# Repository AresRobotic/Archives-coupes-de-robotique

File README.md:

Archives-coupes-de-robotique
============================

Ce dépot contient l'ensemble des documents techniques, codes, cartes et autres des robots des années précédentes.

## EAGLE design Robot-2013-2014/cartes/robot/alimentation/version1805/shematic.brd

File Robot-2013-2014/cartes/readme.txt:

cartes à jour et transmises en fab à Dipole

il faut regenerer toutes les images et tableaux wiki de chaque cartes.

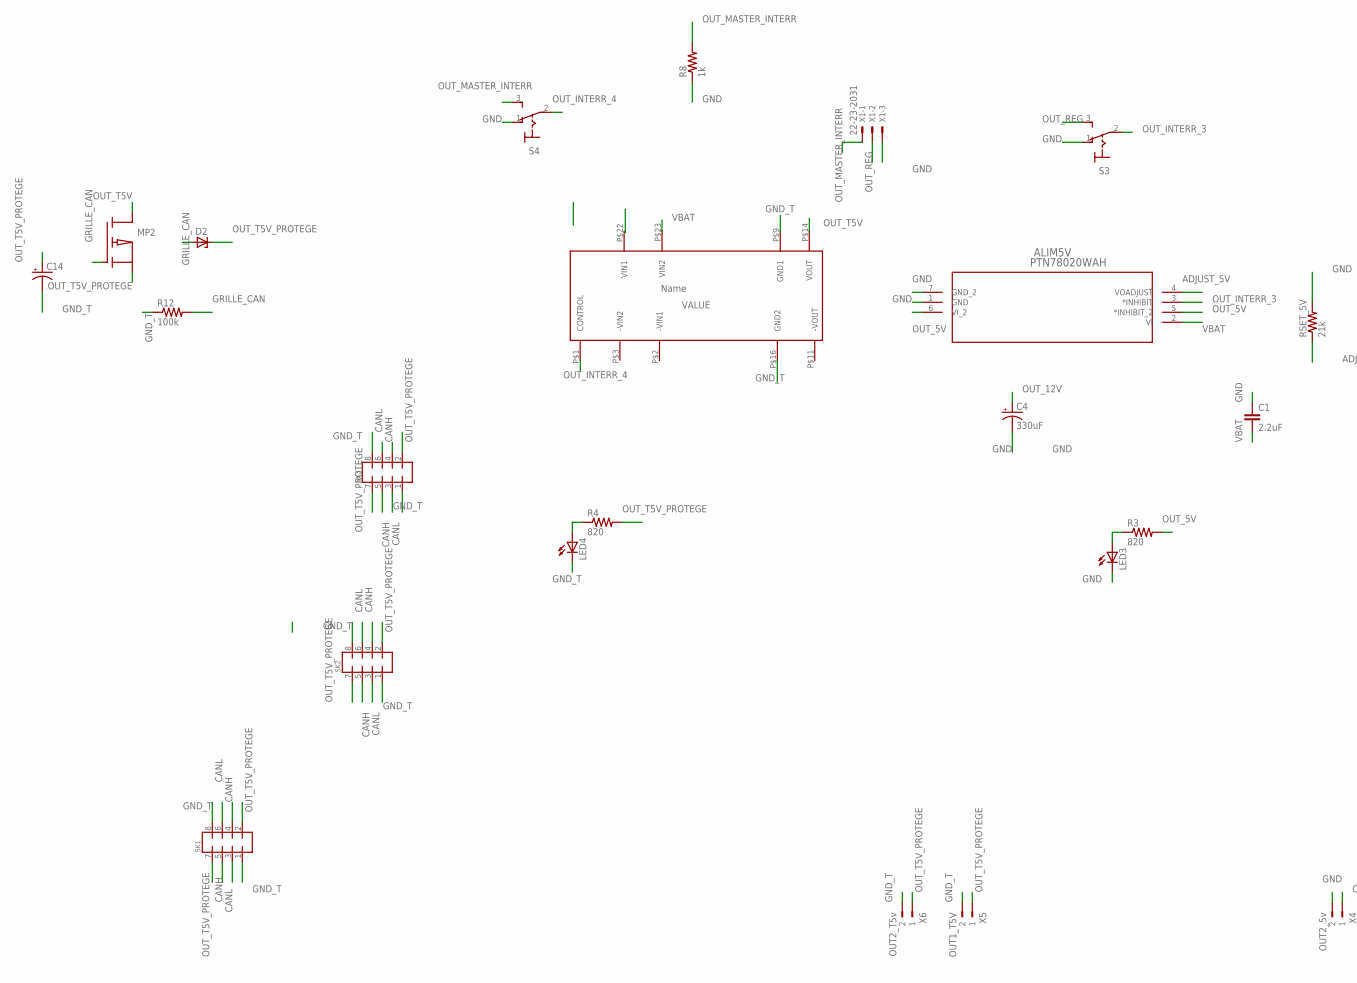
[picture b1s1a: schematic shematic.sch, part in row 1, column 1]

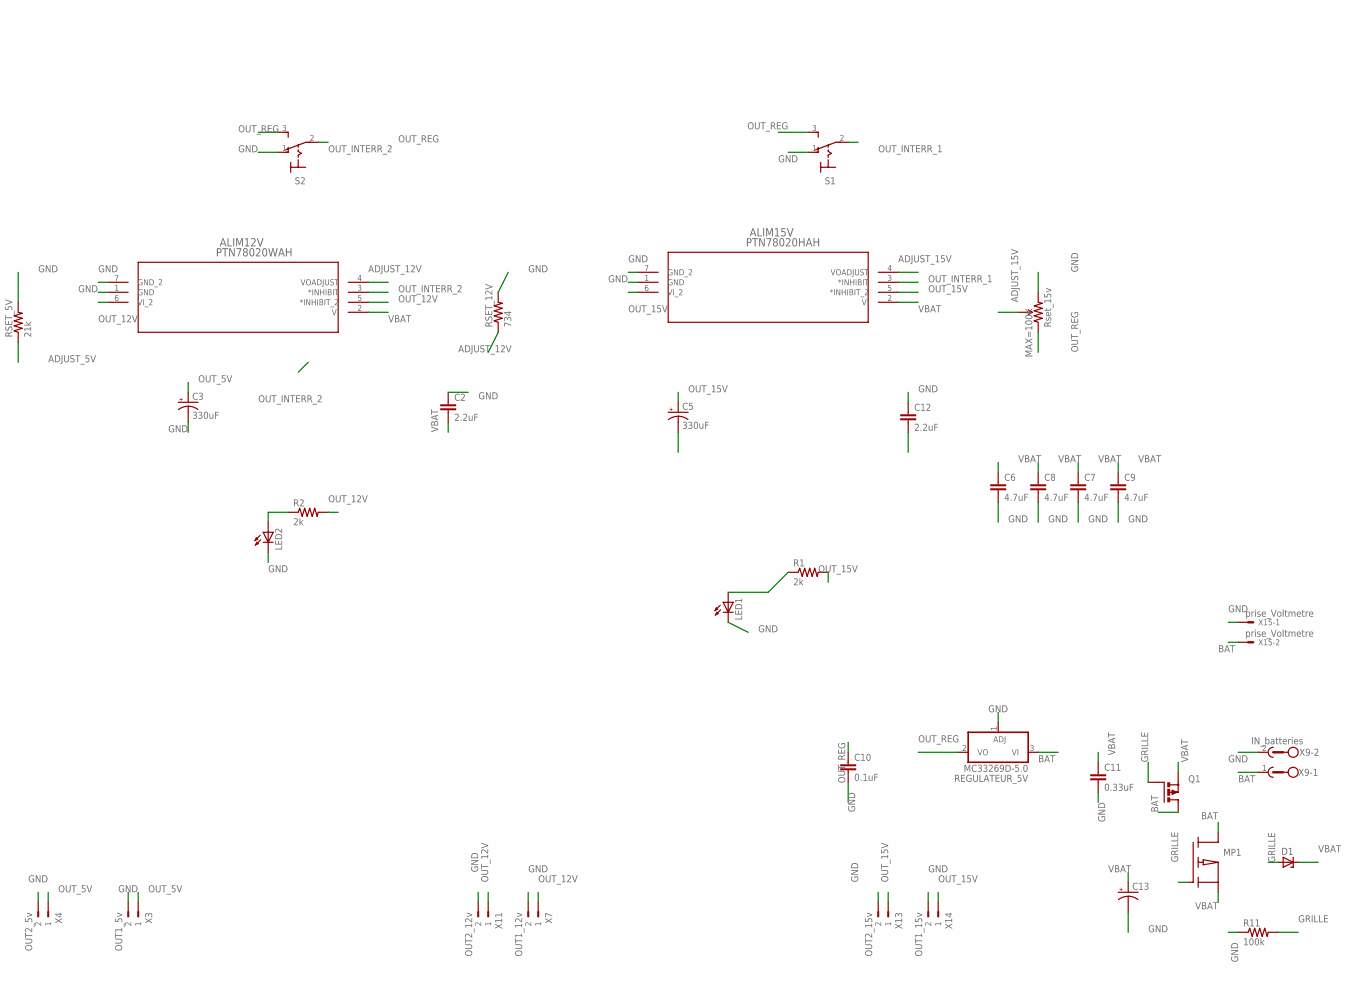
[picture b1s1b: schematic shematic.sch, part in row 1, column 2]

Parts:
ALIM5V, ALIM12V: PTN78020WAH; EUK7
ALIM15V: PTN78020HAH; EUK7
C1, C2, C12: 2.2uF; 0805
C3, C4, C5: 330uF; CPOL-RADIAL-100UF-25V
C6, C7, C8, C9: 4.7uF; 0805
C10: 0.1uF; 0805
C11: 0.33uF; 0805
C13, C14: CAP_POLPTH1; CPOL-RADIAL-100UF-25V
D1, D2: ZENER-DIODESOT23; SOT23
LED1, LED2, LED3, LED4: LEDCHIP-LED0805; CHIP-LED0805
MAX=100K: Rset_15v; 3386U
MP1, MP2: PMOS; SOT23
Q1: PMOSFET_PTO220BH; TO220BH
R1, R2: 2k; 0805
R3, R4: 820; 0805
R8: 1k; 0805
R11, R12: 100k; 0805
REGULATEUR_5V: MC33269D-5.0; DPACK
RSET_5V: 21k; 0805
RSET_12V: 734; 0805
S1, S2, S3, S4: M9040P
SK1, SK2, SK3: MMATCH-8-PTH; AMP-215079-8
U$1: MURATA_NSC12
X1: 22-23-2031
X3: OUT1_5v; 90-2
X4: OUT2_5v; 90-2
X5: OUT1_T5V; 90-2
X6: OUT2_T5v; 90-2
X7: OUT1_12v; 90-2
X9: IN_batteries; GMSTBA2
X11: OUT2_12v; 90-2
X13: OUT2_15v; 90-2
X14: OUT1_15v; 90-2
X15: prise_Voltmetre; KK-156-2

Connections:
ADJUST_5V: ALIM5V.4 (VOADJUST), RSET_5V.1
ADJUST_12V: ALIM12V.4 (VOADJUST), RSET_12V.1
ADJUST_15V: ALIM15V.4 (VOADJUST), MAX=100K.2 (WIPER)
BAT: MP1.3 (D), Q1.D, REGULATEUR_5V.3 (VI), X9.1, X15.2
CANH: SK1.4, SK1.5, SK2.4, SK2.5, SK3.4, SK3.5
CANL: SK1.3, SK1.6, SK2.3, SK2.6, SK3.3, SK3.6
GND: ALIM5V.1 (GND), ALIM5V.7 (GND_2), ALIM12V.1 (GND), ALIM12V.7 (GND_2), ALIM15V.1 (GND), ALIM15V.7 (GND_2), C1.1, C2.1, C3.2 (-), C4.2 (-), C5.2 (-), C6.2, C7.2, C8.2, C9.2, C10.2, C11.2, C12.1, C13.2 (-), LED1.C, LED2.C, LED3.C, MAX=100K.3 (CW), R8.1, R11.1, REGULATEUR_5V.1 (ADJ), RSET_5V.2, RSET_12V.2, S1.1 (O), S2.1 (O), S3.1 (O), S4.1 (O), X1.3, X3.2, X4.2, X7.2, X9.2, X11.2, X13.2, X14.2, X15.1
GND_T: C14.2 (-), LED4.C, R12.1, SK1.1, SK1.8, SK2.1, SK2.8, SK3.1, SK3.8, X5.2, X6.2
GRILLE: D1.1 (A), MP1.1 (G), Q1.G, R11.2
GRILLE_CAN: D2.1 (A), MP2.1 (G), R12.2
unnamed: LED1.A, R1.1
unnamed: LED2.A, R2.1
unnamed: LED3.A, R3.1
unnamed: LED4.A, R4.1
OUT_5V: ALIM5V.5 (*INHIBIT_2), ALIM5V.6 (VI_2), C3.1 (+), R3.2, X3.1, X4.1
OUT_12V: ALIM12V.5 (*INHIBIT_2), ALIM12V.6 (VI_2), C4.1 (+), R2.2, X7.1, X11.1
OUT_15V: ALIM15V.5 (*INHIBIT_2), ALIM15V.6 (VI_2), C5.1 (+), R1.2, X13.1, X14.1
OUT_INTERR_1: ALIM15V.3 (*INHIBIT), S1.2
OUT_INTERR_2: ALIM12V.3 (*INHIBIT), S2.2
OUT_INTERR_3: ALIM5V.3 (*INHIBIT), S3.2
OUT_INTERR_4: S4.2
OUT_MASTER_INTERR: R8.2, S4.3 (S), X1.1
OUT_REG: C10.1, MAX=100K.1 (CCW), REGULATEUR_5V.2 (VO), S1.3 (S), S2.3 (S), S3.3 (S), X1.2
OUT_T5V: MP2.3 (D)
OUT_T5V_PROTEGE: C14.1 (+), D2.3 (C), MP2.2 (S), R4.2, SK1.2, SK1.7, SK2.2, SK2.7, SK3.2, SK3.7, X5.1, X6.1
VBAT: ALIM5V.2 (VI), ALIM12V.2 (VI), ALIM15V.2 (VI), C1.2, C2.2, C6.1, C7.1, C8.1, C9.1, C11.1, C12.2, C13.1 (+), D1.3 (C), MP1.2 (S), Q1.S

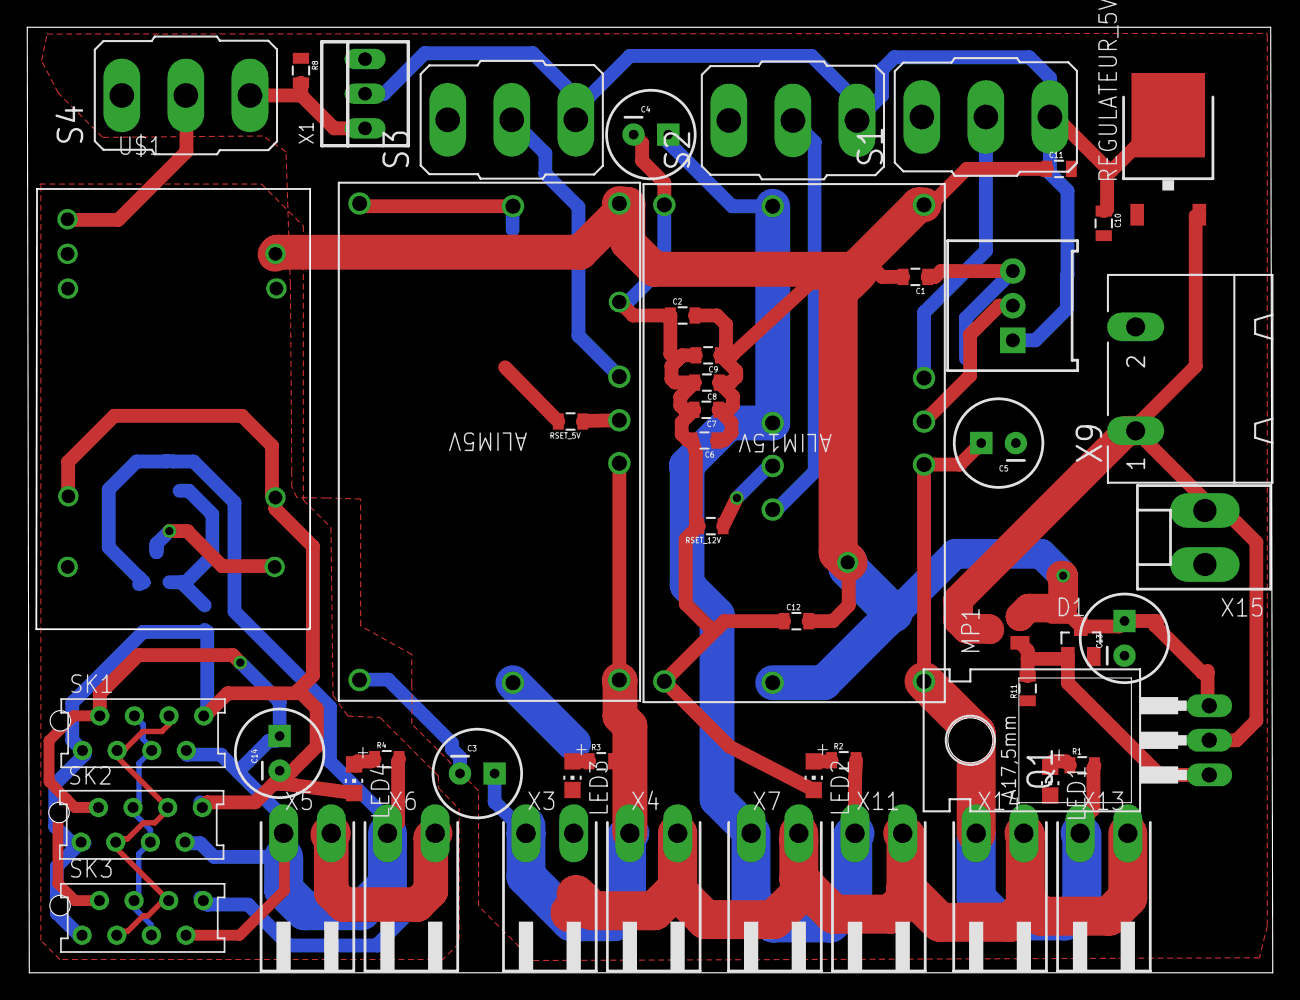
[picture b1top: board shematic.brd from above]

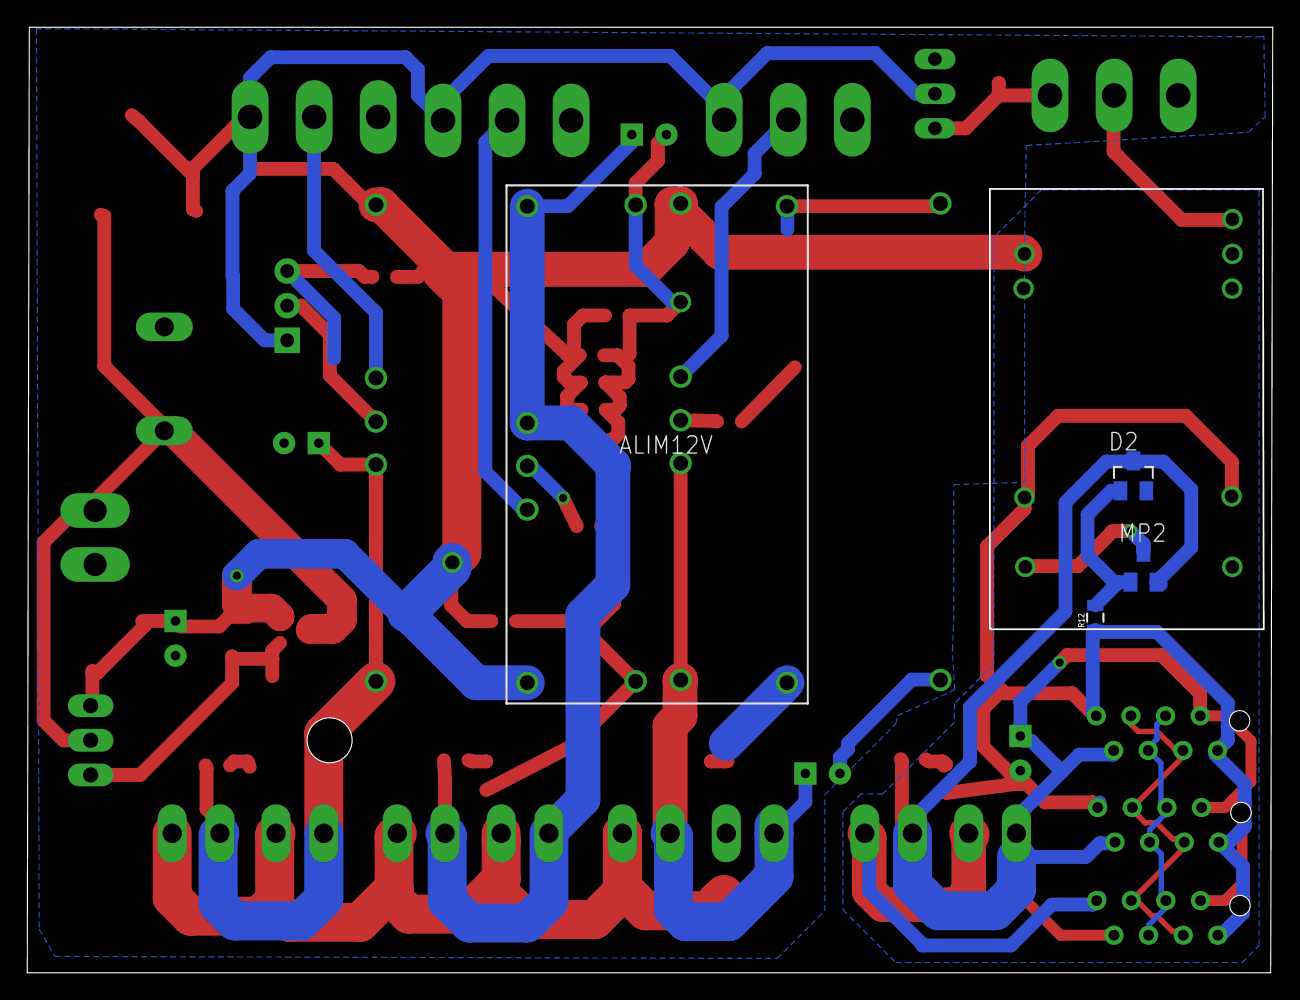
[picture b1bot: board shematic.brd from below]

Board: 2 copper layers, 91.2 x 69.2 mm, 56 parts (4 on the bottom side), 24 nets.

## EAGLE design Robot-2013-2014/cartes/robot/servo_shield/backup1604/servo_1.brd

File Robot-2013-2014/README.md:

Robot-2013-2014
===============

Contient(dra) tous les cartes et codes de l'année 2013-2014

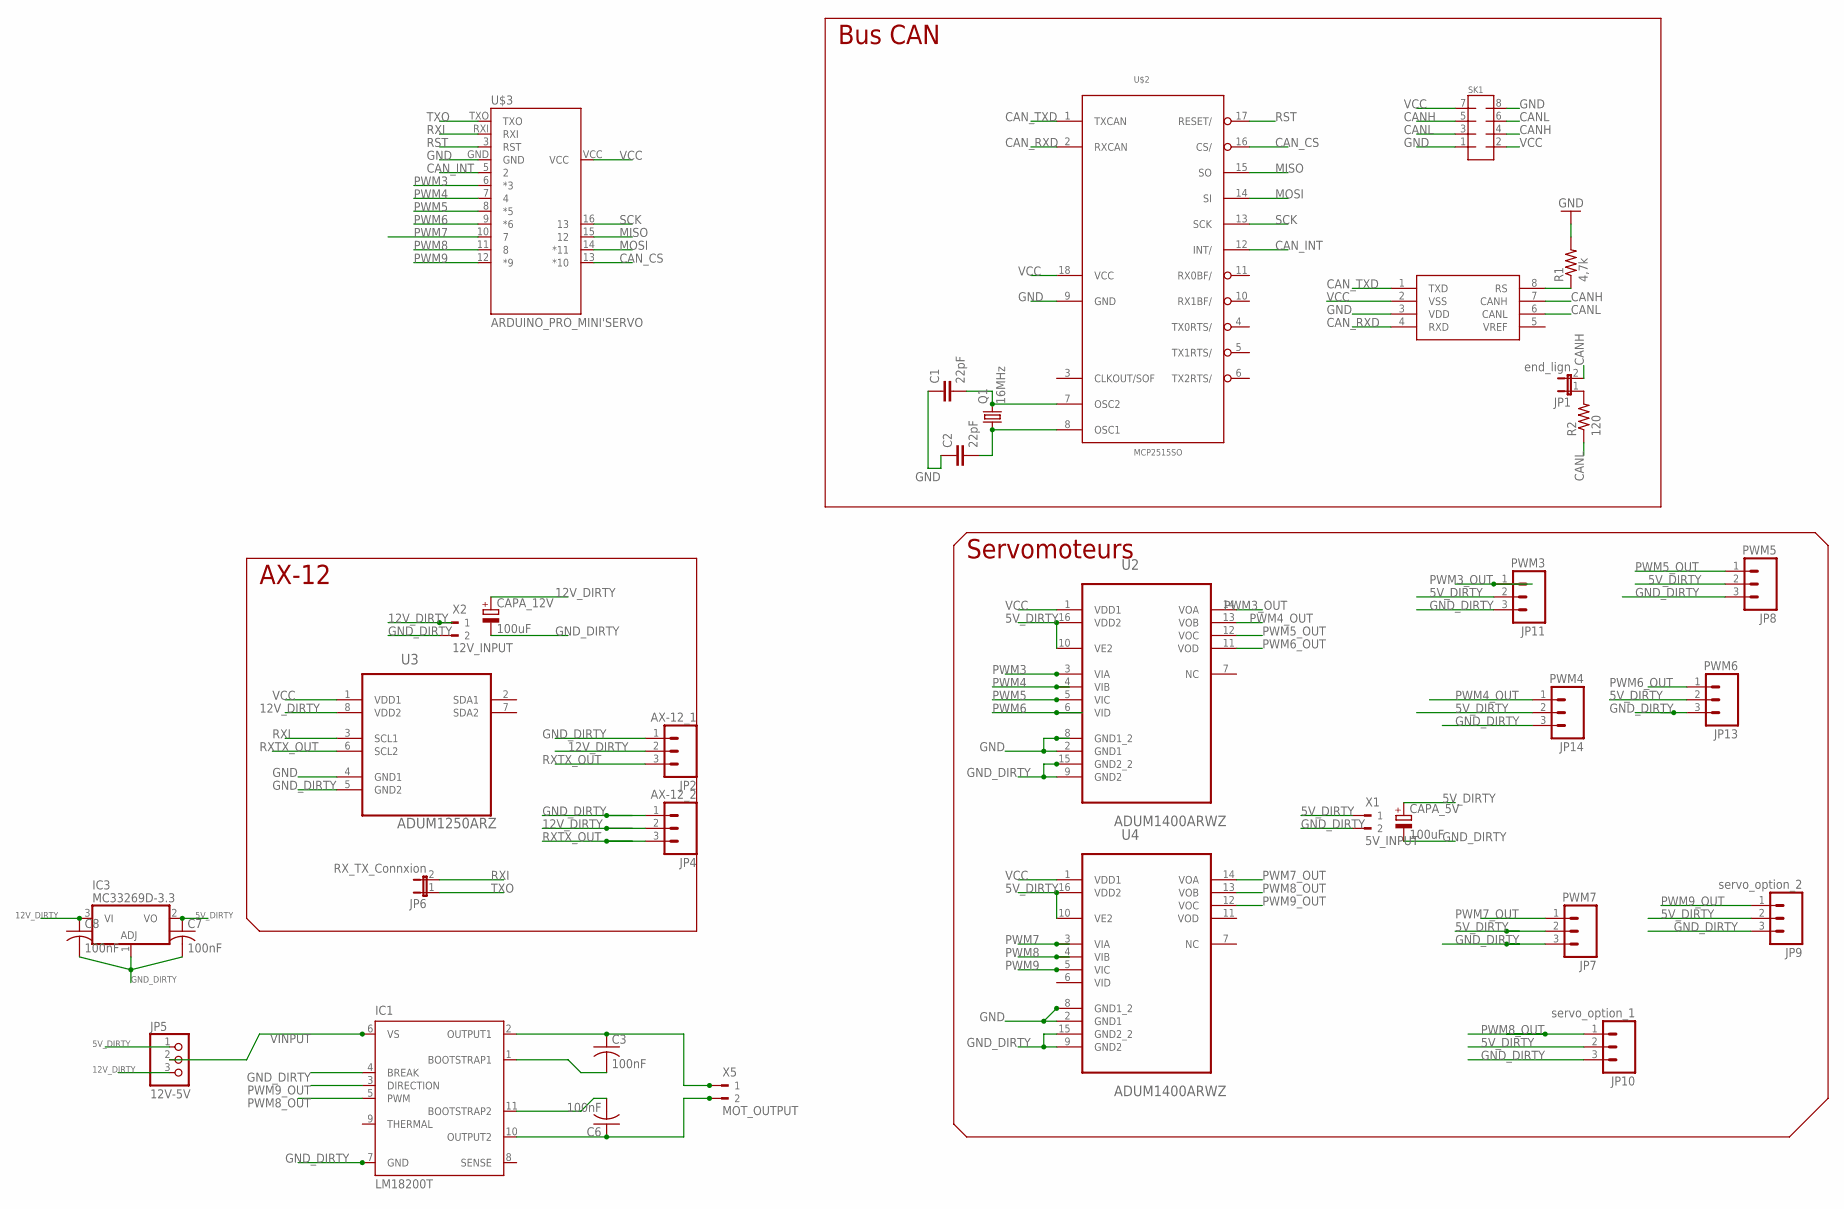
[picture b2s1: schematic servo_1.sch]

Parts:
C1, C2: 22pF; 0805
C3, C6, C7, C8: 100nF; C0805
CAPA_5V, CAPA_12V: 100uF; E5-8,5
IC1: LM18200T; TO-220-11
IC3: MC33269D-3.3; DPACK
JP1: end_lign; 1X02
JP2: AX-12_1; MOLEX-1X3
JP4: AX-12_2; MOLEX-1X3
JP5: 12V-5V; 1X03
JP6: RX_TX_Connxion; 1X02
JP7: PWM7; 1X03
JP8: PWM5; 1X03
JP9: servo_option_2; 1X03
JP10: servo_option_1; 1X03
JP11: PWM3; 1X03
JP13: PWM6; 1X03
JP14: PWM4; 1X03
Q1: 16MHz; HC49/S
R1: 4,7k; 0805
R2: 120; 0805
SK1: MMATCH-8-PTH; AMP-215079-8
U1: MCP2551; SO08
U2, U4: ADUM1400ARWZ; SOIC127P1032X265-16N
U3: ADUM1250ARZ; SOIC127P600X175-8N
U$2: MCP2515SO; SO18L
U$3: ARDUINO_PRO_MINI'SERVO; ARDUINO_PRO_MINI
X1: 5V_INPUT; 90-2
X2: 12V_INPUT; 90-2
X5: MOT_OUTPUT; 90-2

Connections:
5V_DIRTY: C7.1, CAPA_5V.+, IC3.2 (VO), JP5.1, JP7.2, JP8.2, JP9.2, JP10.2, JP11.2, JP13.2, JP14.2, U2.10 (VE2), U2.16 (VDD2), U4.10 (VE2), U4.16 (VDD2), X1.1
12V_DIRTY: C8.1, CAPA_12V.+, IC3.3 (VI), JP2.2, JP4.2, JP5.3, U3.8 (VDD2), X2.1
CANH: JP1.2, SK1.4, SK1.5, U1.7 (CANH)
CANL: R2.1, SK1.3, SK1.6, U1.6 (CANL)
CAN_CS: U$2.16 (CS/), U$3.13 (*10)
CAN_INT: U$2.12 (INT/), U$3.5 (2)
CAN_RXD: U1.4 (RXD), U$2.2 (RXCAN)
CAN_TXD: U1.1 (TXD), U$2.1 (TXCAN)
GND: C1.1, C2.1, R1.2, SK1.1, SK1.8, U1.3 (VDD), U2.2 (GND1), U2.8 (GND1_2), U3.4 (GND1), U4.2 (GND1), U4.8 (GND1_2), U$2.9 (GND), U$3.GND
GND_DIRTY: C7.2, C8.2, CAPA_5V.-, CAPA_12V.-, IC1.4 (BREAK), IC1.7 (GND), IC3.1 (ADJ), JP2.1, JP4.1, JP7.3, JP8.3, JP9.3, JP10.3, JP11.3, JP13.3, JP14.3, U2.9 (GND2), U2.15 (GND2_2), U3.5 (GND2), U4.9 (GND2), U4.15 (GND2_2), X1.2, X2.2
MISO: U$2.15 (SO), U$3.15 (12)
MOSI: U$2.14 (SI), U$3.14 (*11)
unnamed: C3.2, IC1.1 (BOOTSTRAP1)
unnamed: C1.2, Q1.2, U$2.7 (OSC2)
unnamed: C2.2, Q1.1, U$2.8 (OSC1)
unnamed: C6.2, IC1.11 (BOOTSTRAP2)
unnamed: R1.1, U1.8 (RS)
unnamed: JP1.1, R2.2
unnamed: C3.1, IC1.2 (OUTPUT1), X5.1
unnamed: C6.1, IC1.10 (OUTPUT2), X5.2
PWM3: U2.3 (VIA), U$3.6 (*3)
PWM3_OUT: JP11.1, U2.14 (VOA)
PWM4: U2.4 (VIB), U$3.7 (4)
PWM4_OUT: JP14.1, U2.13 (VOB)
PWM5: U2.5 (VIC), U$3.8 (*5)
PWM5_OUT: JP8.1, U2.12 (VOC)
PWM6: U2.6 (VID), U$3.9 (*6)
PWM6_OUT: JP13.1, U2.11 (VOD)
PWM7: U4.3 (VIA), U$3.10 (7)
PWM7_OUT: JP7.1, U4.14 (VOA)
PWM8: U4.4 (VIB), U$3.11 (8)
PWM8_OUT: IC1.5 (PWM), JP10.1, U4.13 (VOB)
PWM9: U4.5 (VIC), U$3.12 (*9)
PWM9_OUT: IC1.3 (DIRECTION), JP9.1, U4.12 (VOC)
RST: U$2.17 (RESET/), U$3.3 (RST)
RXI: JP6.2, U3.3 (SCL1), U$3.RXI
RXTX_OUT: JP2.3, JP4.3, U3.6 (SCL2)
SCK: U$2.13 (SCK), U$3.16 (13)
TXO: JP6.1, U$3.TXO
VCC: SK1.2, SK1.7, U1.2 (VSS), U2.1 (VDD1), U3.1 (VDD1), U4.1 (VDD1), U$2.18 (VCC), U$3.VCC
VINPUT: IC1.6 (VS), JP5.2

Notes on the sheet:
Bus CAN
AX-12
Servomoteurs

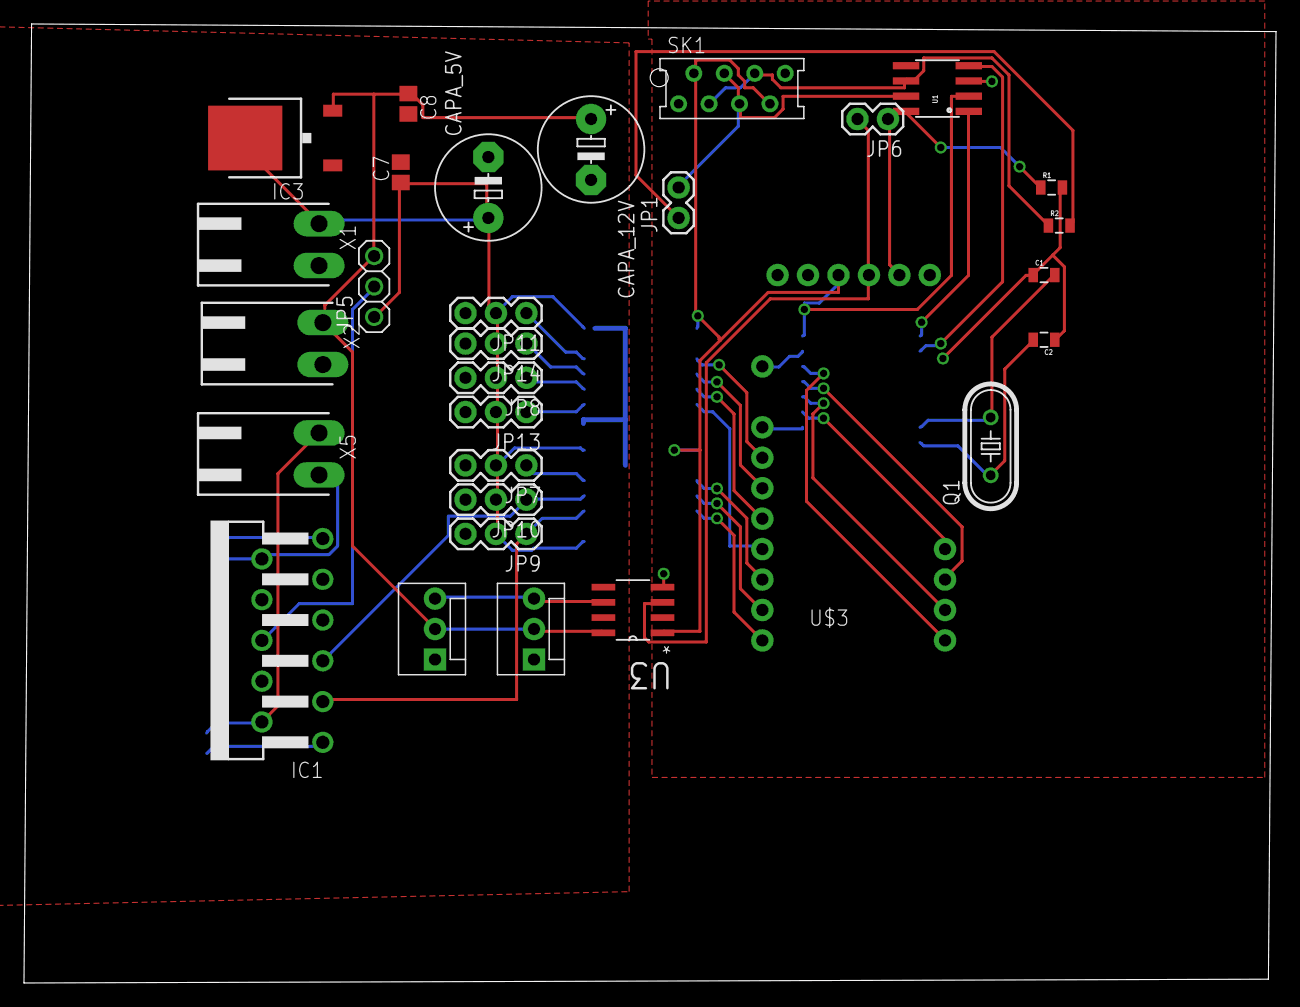
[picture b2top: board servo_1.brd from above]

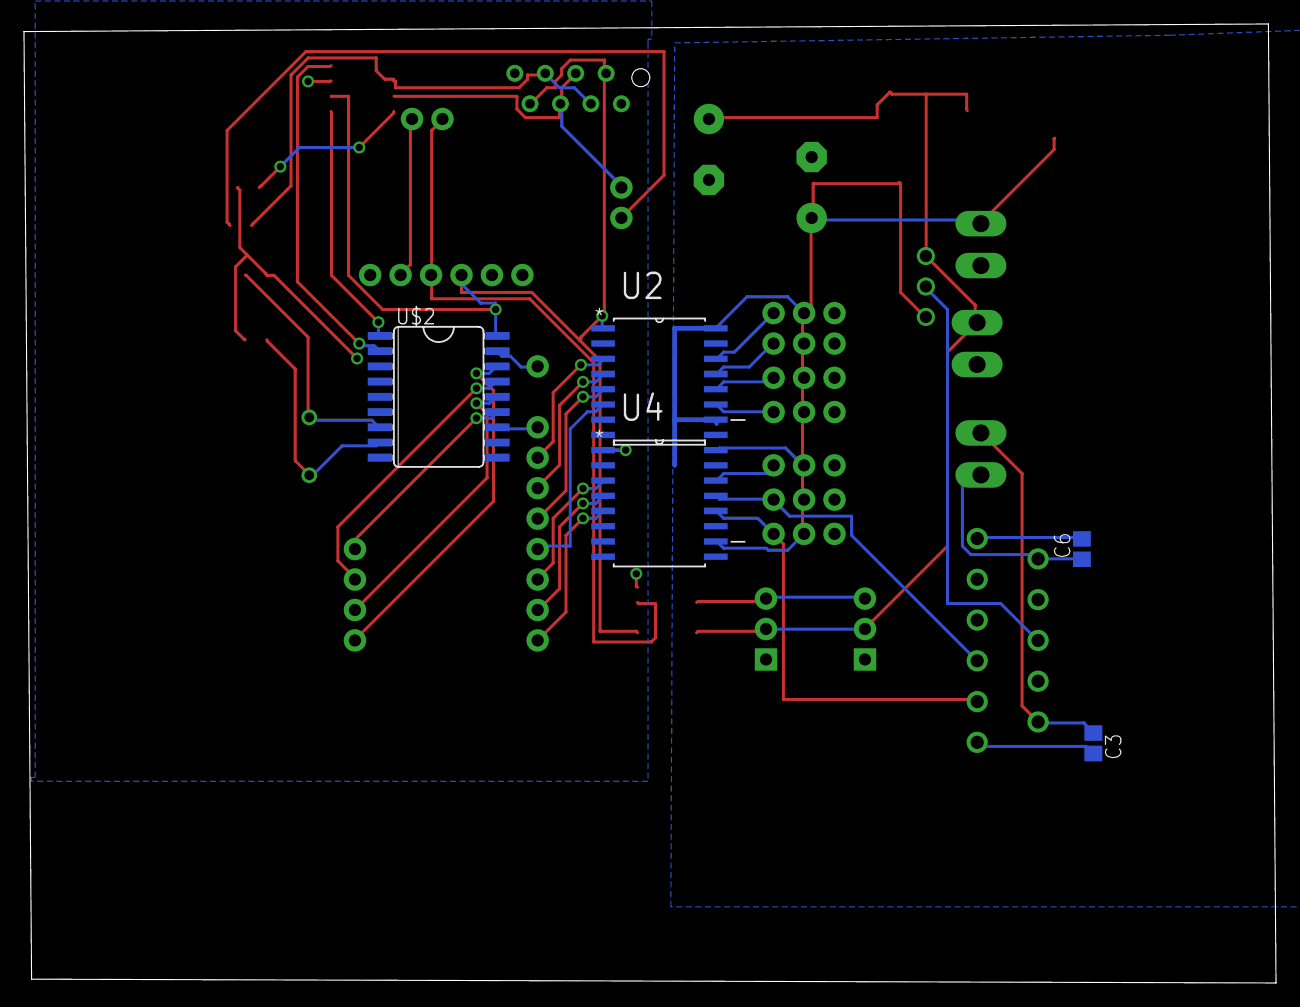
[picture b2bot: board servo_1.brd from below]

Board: 2 copper layers, 104.4 x 80.0 mm, 35 parts (5 on the bottom side), 41 nets.

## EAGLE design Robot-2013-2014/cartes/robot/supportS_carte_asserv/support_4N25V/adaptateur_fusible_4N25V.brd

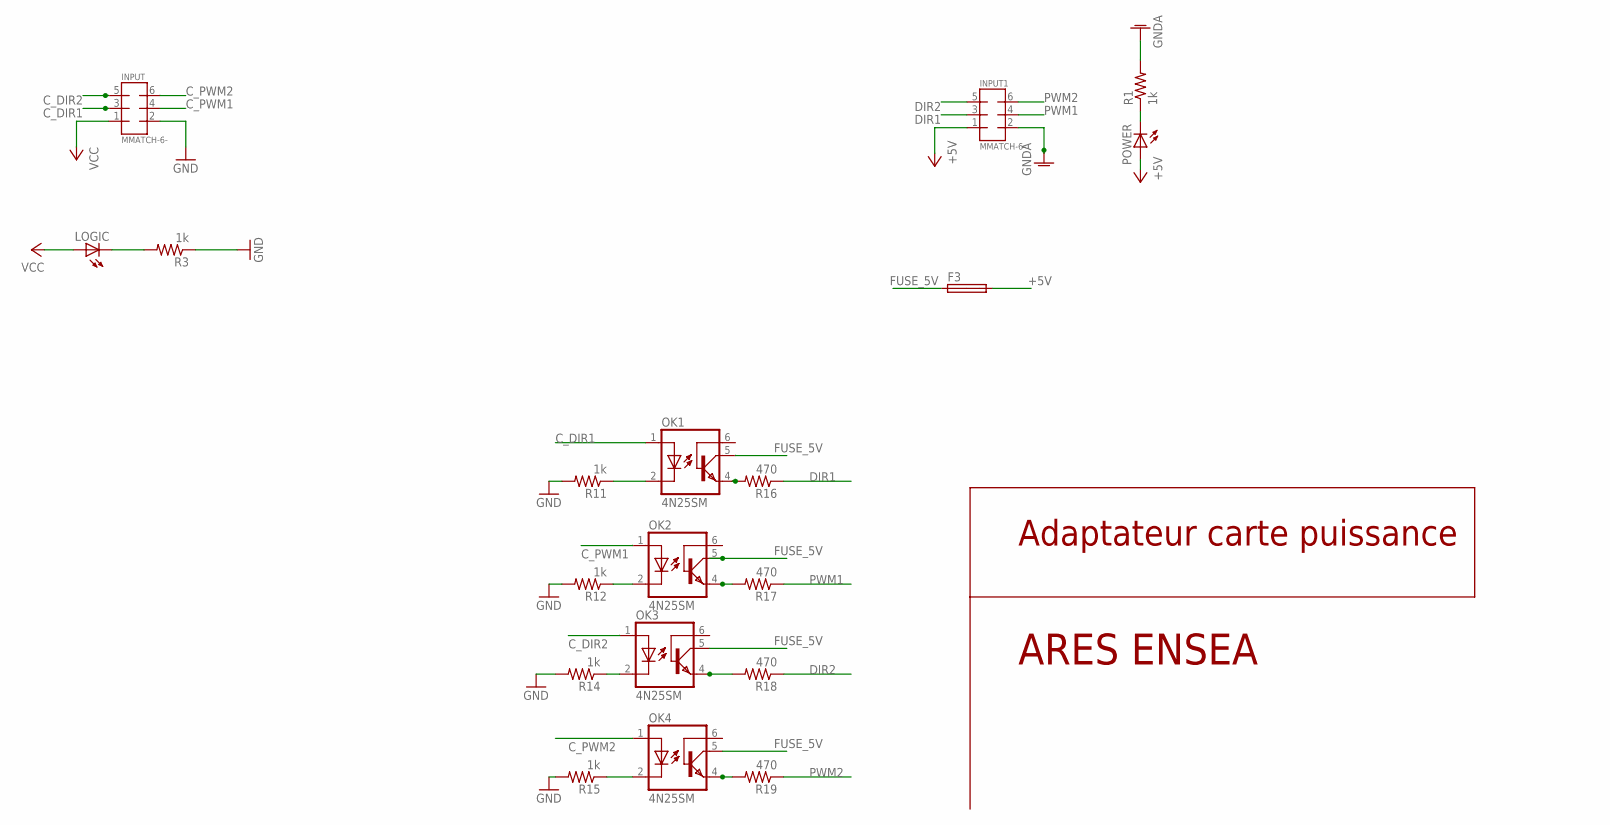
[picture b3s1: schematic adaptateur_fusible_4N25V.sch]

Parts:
F3: SHK20L
INPUT, INPUT1: MMATCH-6-; AMP-215079-6
LOGIC: LEDSML0805; SML0805
OK1, OK2, OK3, OK4: 4N25SM; DIL6-SMD
POWER: LEDSML0805; SML0805
R1, R3, R11, R12, R14, R15: 1k; M0805
R16, R17, R18, R19: 470; M0805

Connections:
+5V: F3.2A, INPUT1.1 (3), POWER.A
C_DIR1: INPUT.3 (5), OK1.1 (A)
C_DIR2: INPUT.5 (7), OK3.1 (A)
C_PWM1: INPUT.4 (6), OK2.1 (A)
C_PWM2: INPUT.6 (8), OK4.1 (A)
DIR1: INPUT1.3 (5), R16.1
DIR2: INPUT1.5 (7), R18.1
FUSE_5V: F3.1A, OK1.5 (COL), OK2.5 (COL), OK3.5 (COL), OK4.5 (COL)
GND: INPUT.2 (4), R3.1, R11.2, R12.2, R14.2, R15.2
GNDA: INPUT1.2 (4), R1.2
unnamed: OK1.2 (C), R11.1
unnamed: OK2.2 (C), R12.1
unnamed: POWER.C, R1.1
unnamed: LOGIC.C, R3.2
unnamed: OK3.2 (C), R14.1
unnamed: OK4.2 (C), R15.1
unnamed: OK1.4 (EMI), R16.2
unnamed: OK2.4 (EMI), R17.2
unnamed: OK3.4 (EMI), R18.2
unnamed: OK4.4 (EMI), R19.2
PWM1: INPUT1.4 (6), R17.1
PWM2: INPUT1.6 (8), R19.1
VCC: INPUT.1 (3), LOGIC.A

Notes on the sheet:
ARES ENSEA
Adaptateur carte puissance

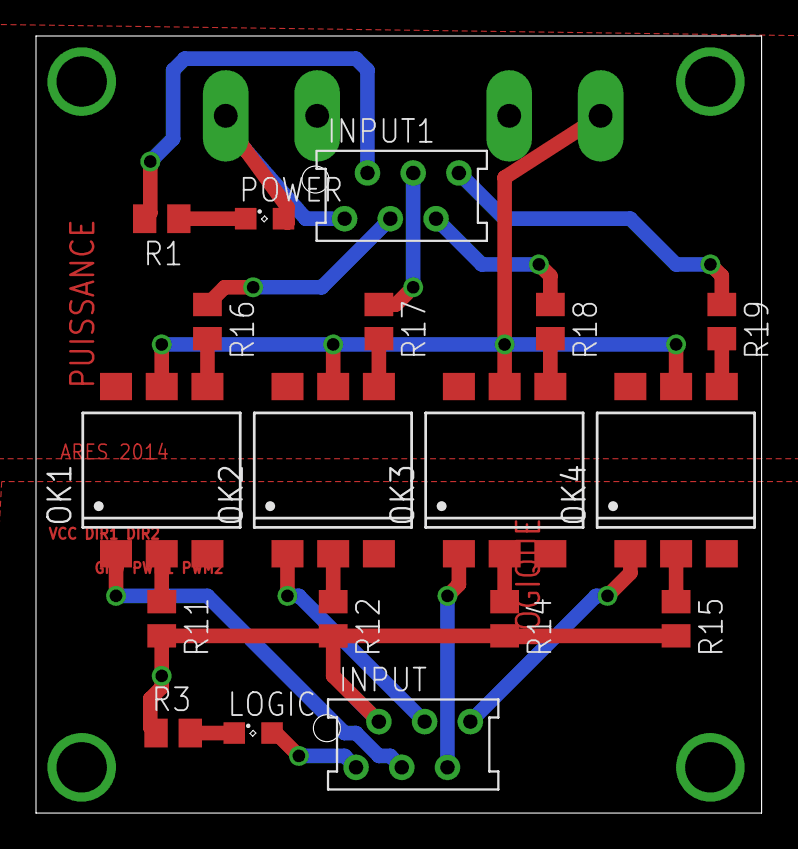
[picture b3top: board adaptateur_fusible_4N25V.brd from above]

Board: 2 copper layers, 40.3 x 43.2 mm, 19 parts (1 on the bottom side), 23 nets.

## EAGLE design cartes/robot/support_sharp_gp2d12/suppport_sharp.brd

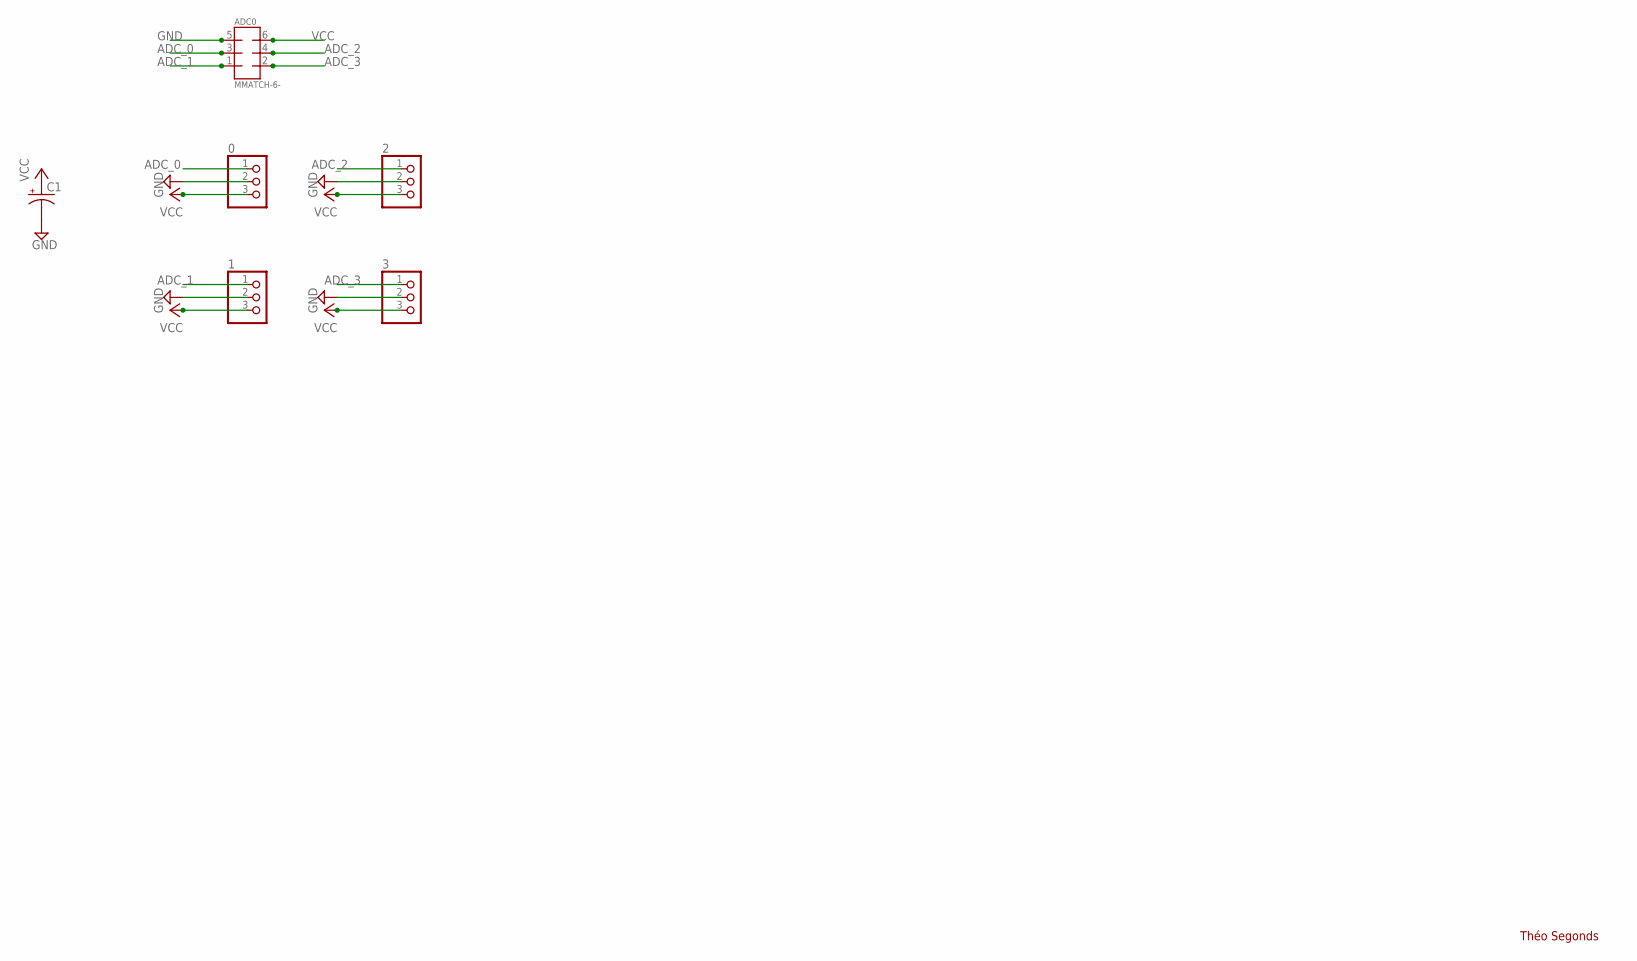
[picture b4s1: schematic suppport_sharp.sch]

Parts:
0, 1, 2, 3: PINHD-1X3; 1X03
ADC0: MMATCH-6-; AMP-215079-6
C1: CAP_POLPTH1; CPOL-RADIAL-100UF-25V

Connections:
ADC_0: 0.1, ADC0.3 (5)
ADC_1: 1.1, ADC0.1 (3)
ADC_2: 2.1, ADC0.4 (6)
ADC_3: 3.1, ADC0.2 (4)
GND: 0.2, 1.2, 2.2, 3.2, ADC0.5 (7), C1.2 (-)
VCC: 0.3, 1.3, 2.3, 3.3, ADC0.6 (8), C1.1 (+)

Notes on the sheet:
Théo Segonds

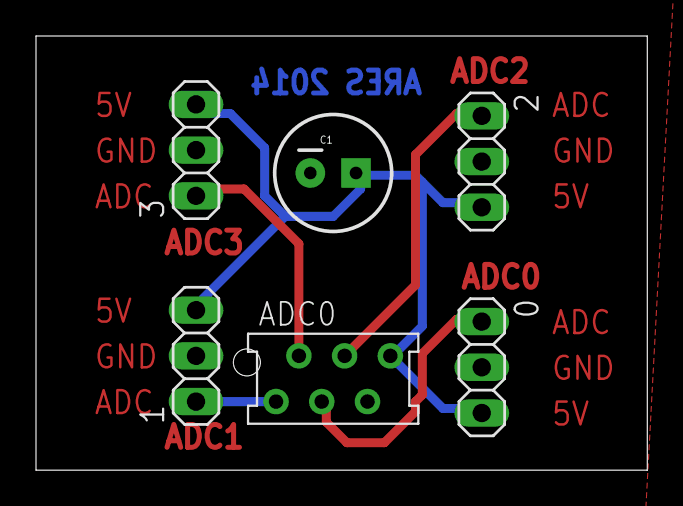
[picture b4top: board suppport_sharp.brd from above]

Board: 2 copper layers, 34.0 x 24.1 mm, 6 parts (0 on the bottom side), 6 nets.

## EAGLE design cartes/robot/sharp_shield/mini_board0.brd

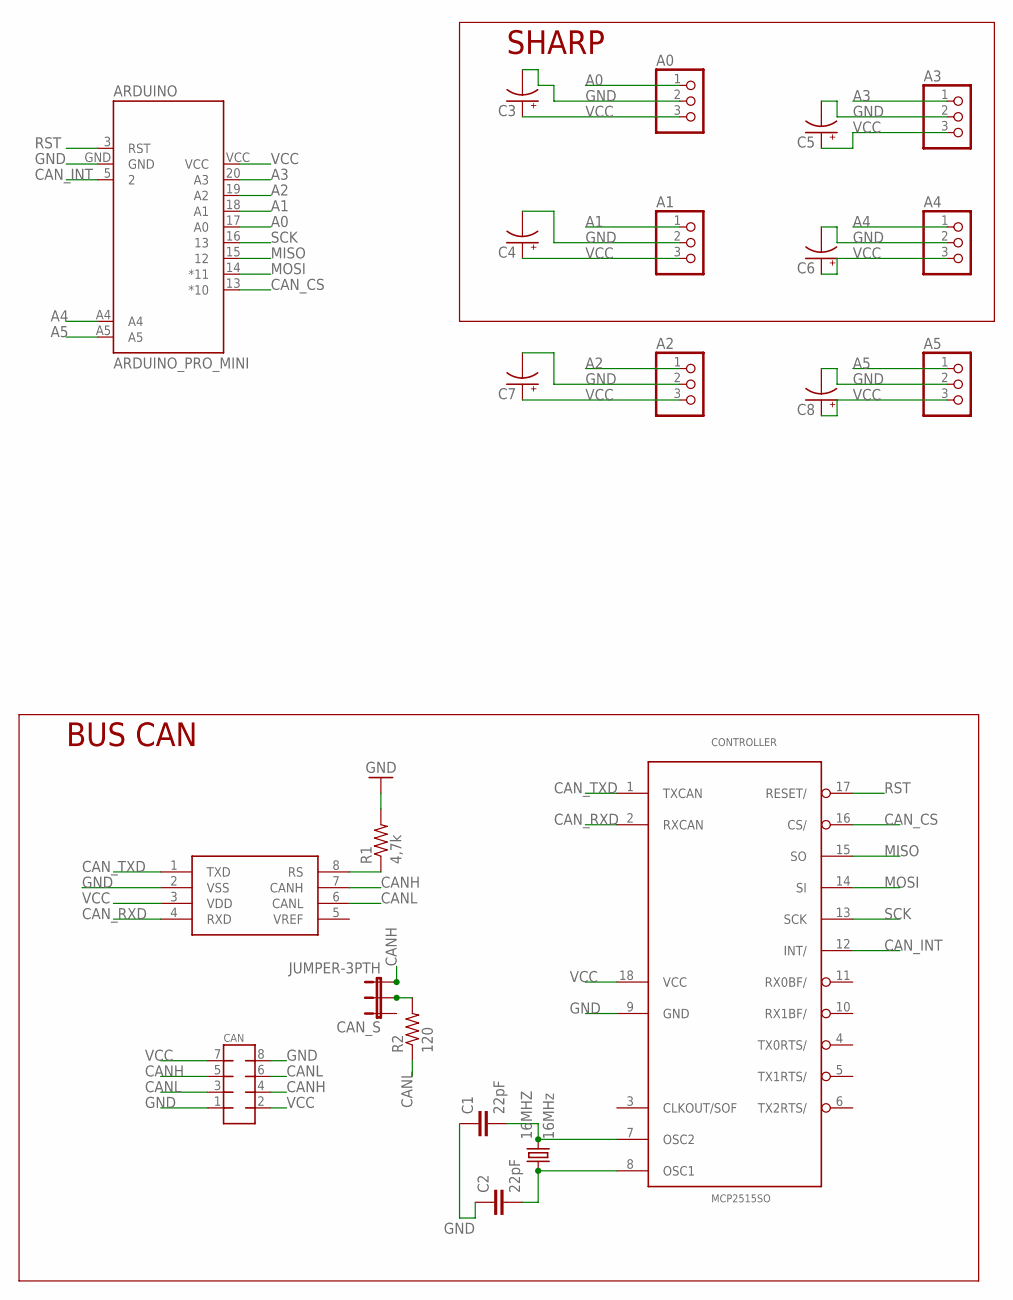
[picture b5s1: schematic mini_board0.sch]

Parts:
16MHZ: 16MHz; HC49/S
A0, A1, A2, A3, A4, A5: PINHD-1X3/90; 1X03/90
ARDUINO: ARDUINO_PRO_MINI
C1, C2: 22pF; 0805
C3, C4, C5, C6, C7, C8: CAP_POLPTH2; CPOL-RADIAL-10UF-25V
CAN: MMATCH-8-PTH; AMP-215079-8
CAN_S: JUMPER-3PTH; 1X03
CONTROLLER: MCP2515SO; SO18L
R1: 4,7k; 0805
R2: 120; 0805
U1: MCP2551; SO08

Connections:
A0: A0.1, ARDUINO.17 (A0)
A1: A1.1, ARDUINO.18 (A1)
A2: A2.1, ARDUINO.19 (A2)
A3: A3.1, ARDUINO.20 (A3)
A4: A4.1, ARDUINO.A4
A5: A5.1, ARDUINO.A5
CANH: CAN.4, CAN.5, CAN_S.3, U1.7 (CANH)
CANL: CAN.3, CAN.6, R2.1, U1.6 (CANL)
CAN_CS: ARDUINO.13 (*10), CONTROLLER.16 (CS/)
CAN_INT: ARDUINO.5 (2), CONTROLLER.12 (INT/)
CAN_RXD: CONTROLLER.2 (RXCAN), U1.4 (RXD)
CAN_TXD: CONTROLLER.1 (TXCAN), U1.1 (TXD)
GND: A0.2, A1.2, A2.2, A3.2, A4.2, A5.2, ARDUINO.GND, C1.1, C2.1, C3.2 (-), C4.2 (-), C5.2 (-), C6.2 (-), C7.2 (-), C8.2 (-), CAN.1, CAN.8, CONTROLLER.9 (GND), R1.2, U1.2 (VSS)
MISO: ARDUINO.15 (12), CONTROLLER.15 (SO)
MOSI: ARDUINO.14 (*11), CONTROLLER.14 (SI)
unnamed: 16MHZ.2, C1.2, CONTROLLER.7 (OSC2)
unnamed: 16MHZ.1, C2.2, CONTROLLER.8 (OSC1)
unnamed: R1.1, U1.8 (RS)
unnamed: CAN_S.2, R2.2
RST: ARDUINO.3 (RST), CONTROLLER.17 (RESET/)
SCK: ARDUINO.16 (13), CONTROLLER.13 (SCK)
VCC: A0.3, A1.3, A2.3, A3.3, A4.3, A5.3, ARDUINO.VCC, C3.1 (+), C4.1 (+), C5.1 (+), C6.1 (+), C7.1 (+), C8.1 (+), CAN.2, CAN.7, CONTROLLER.18 (VCC), U1.3 (VDD)

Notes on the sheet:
BUS CAN
SHARP

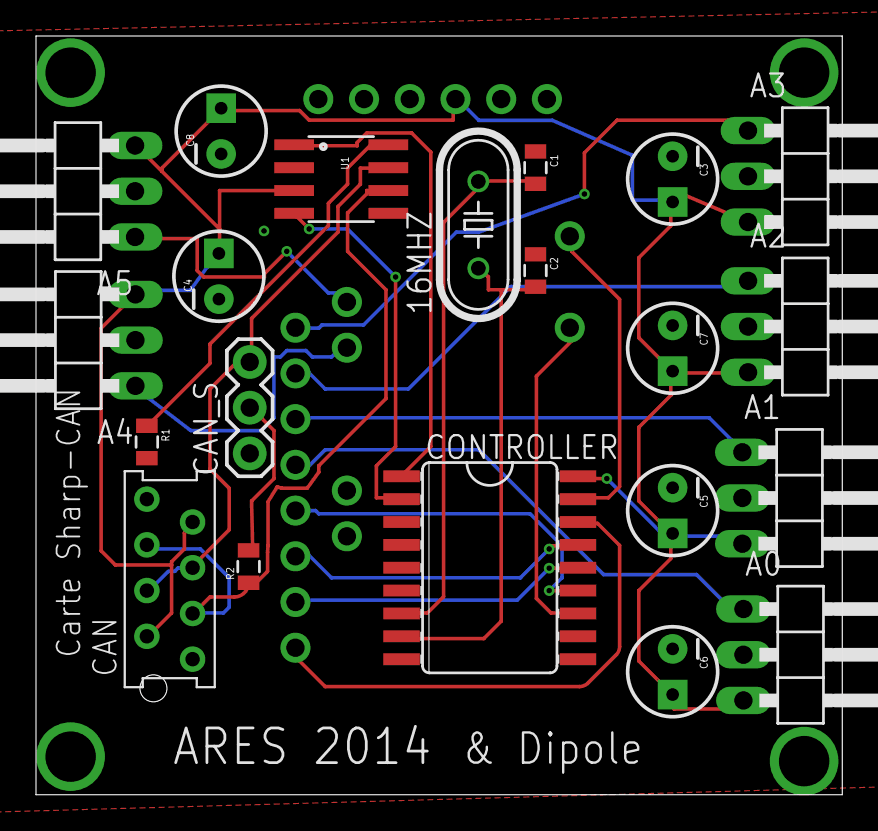
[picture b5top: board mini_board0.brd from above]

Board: 2 copper layers, 44.8 x 42.2 mm, 22 parts (1 on the bottom side), 22 nets.

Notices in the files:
parts and their libraries:
SparkFun-Resistors: Licensing: CC v3.0 Share-Alike You are welcome to use this library for commercial purposes.
